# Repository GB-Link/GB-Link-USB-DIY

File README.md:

# GB-Link USB DIY: USB TO GAME BOY LINK ADAPTER

An Open-Source USB to Gameboy Link Cable Adapter for Raspberry Pi Pico. Designed with components that are easy to source and solder. Original design by agtbaskara. Link port footprint added by fairy0715. 
This board allows you to connect to GB/C or GBA games using a gereric GBC cable. OEM cables will work with their expected games.

# Required Components

| Reference | Part Number | Description |
|-|-|-|
| U1 | [Raspberry Pi Pico](https://www.raspberrypi.com/products/raspberry-pi-pico/) | Clones are compatible |
| U2 | [BOB-12009](https://www.sparkfun.com/products/12009) | Sparkfun Bi-Directional Logic Level Converter, clones are compatible |
| SW1 | [SS12D00-G3](https://www.amazon.com/Tnuocke-Vertical-Position-Switches-SS12D00-G3/dp/B099MRCDG8) | 3 Pin SPDT Switch with 1" (2.54mm) Pitch |

# Optional Case
Optional case available to print, works well in either PLA or PETG. No screws or glue needed.

https://www.printables.com/model/1805845-gb-link-v11-housing

# How to Order Board

To order a board, use the `gerbers.zip` from the release page or generate one yourself. You can order from your favourite PCB manufacturer ([JLCPCB](https://jlcpcb.com/), [PCBWay](https://www.pcbway.com/), etc.).

**Use 1.2mm PCB thickness.**

You can choose any colour for the Solder Mask and Silkscreen. For the Surface Finish, ENIG is highly recommended.

# How to Assemble Board

1. Sand the PCB edge connectors if necessary.
2. Solder pin header to Raspberry Pi Pico and Level Shifter module. Use a breadboard for easier pin soldering.
3. Solder Raspberry Pi Pico and Level Shifter module to the board
5. Solder the 1x3 Pin Header to the board, and place the Pin Jumper
6. Flash firmware to your Raspberry Pi Pico

Recomended firmware:
- [https://github.com/GB-Link/GBLink-Firmware/releases](https://github.com/GB-Link/GBLink-Firmware/releases)
List of clients for the GB-Link firmware found at [https://launcher.gblink.io/](https://launcher.gblink.io/)

Other compatible firmware:
- https://github.com/Celio-Link/Celio-Firmware
- https://github.com/Lorenzooone/pico-gb-mobile-adapter
- https://github.com/starlarkus/gb-link-firmware-reconfigurable
- https://github.com/stacksmashing/gb-link-firmware
- https://github.com/stacksmashing/gb-link-printer
- https://github.com/dj505/GBPrinterEmu
- https://github.com/Squaresweets/GBPrinter-discord-bot
- https://github.com/KuestenKeks/pc-to-gb-printer

- Raspberry Pi Pico Footprint: https://github.com/ncarandini/KiCad-RP-Pico
- Logic Level Converter (BOB-12009) Footprint: https://www.snapeda.com/parts/BOB-12009/SparkFun%20Electronics/view-part/
- Gameboy Link Connector Footprint: https://github.com/Palmr/gb-link-cable
- 1.2mm PCB Thickness, based on: https://hackaday.io/project/12932-game-link-online/log/43999-received-the-breakout-boards

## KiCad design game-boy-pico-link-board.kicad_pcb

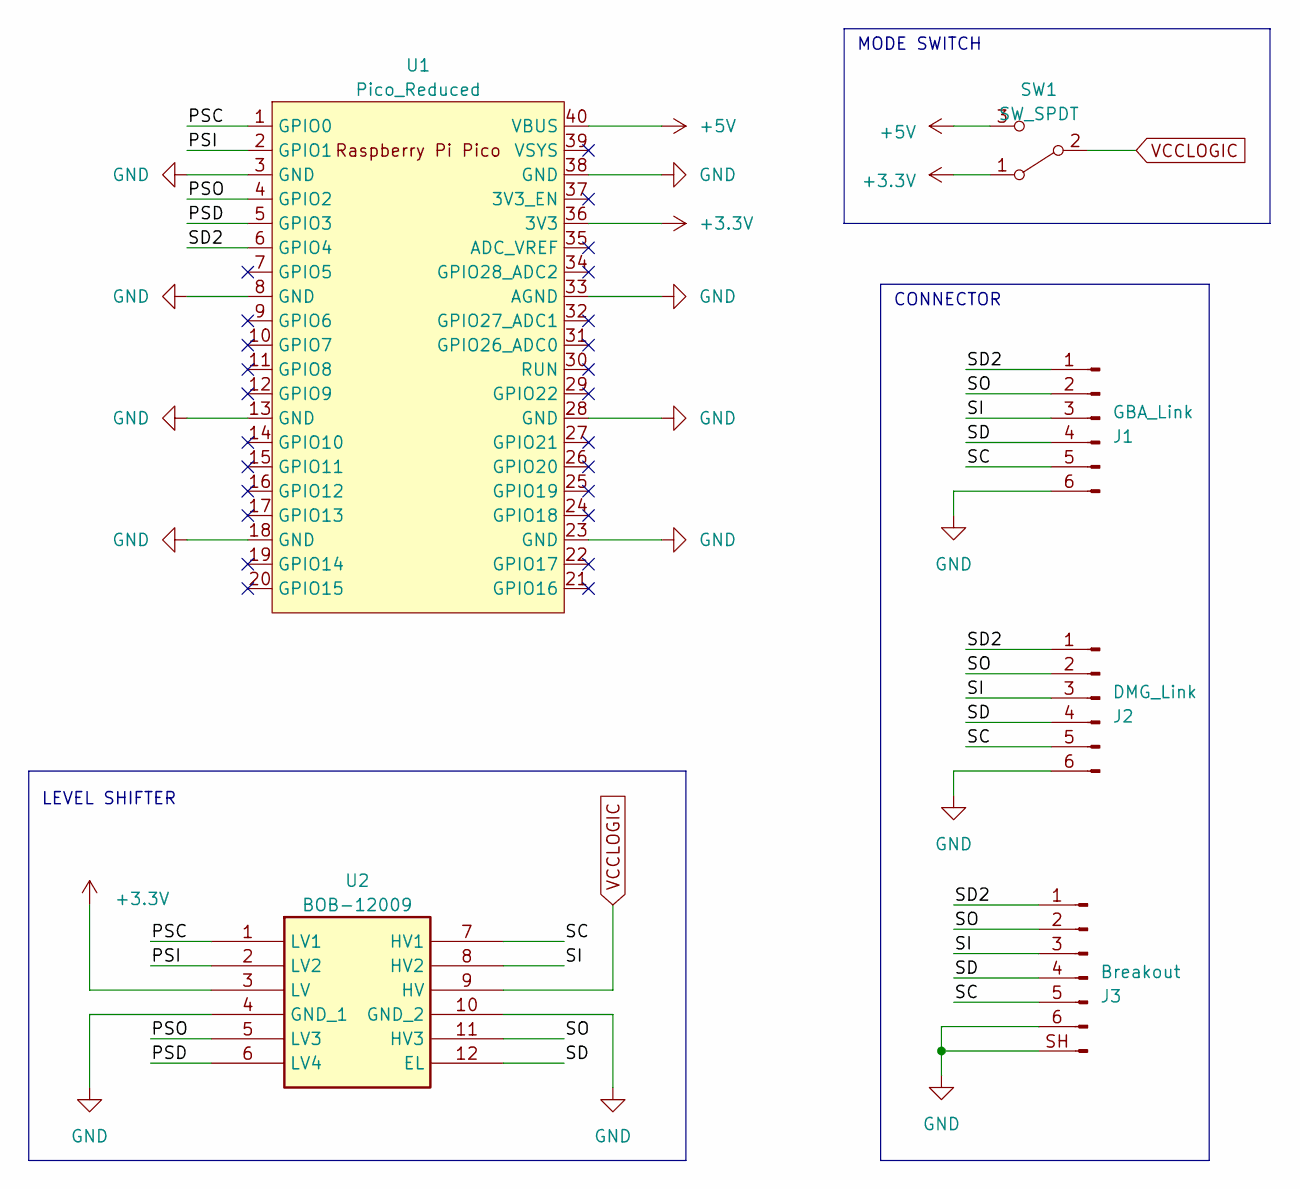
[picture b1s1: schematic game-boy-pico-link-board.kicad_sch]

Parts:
J1: GBA_Link; gb-link-socket
J2: DMG_Link; dmg-link-socket
J3: Breakout; gba_linkport
SW1: SW_SPDT; PinHeader_1x03_P2.54mm_Vertical
U1: Pico_Reduced; RPi_Pico_SMD_TH_REDUCED
U2: BOB-12009

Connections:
+3.3V: SW1.1 (A), U1.36 (3V3), U2.3 (LV)
+5V: SW1.3 (C), U1.40 (VBUS)
/GBVCC: J1.1, J2.1, J3.1, U1.6 (GPIO4)
/PSC: U1.1 (GPIO0), U2.1 (LV1)
/PSD: U1.5 (GPIO3), U2.6 (LV4)
/PSI: U1.2 (GPIO1), U2.2 (LV2)
/PSO: U1.4 (GPIO2), U2.5 (LV3)
/SC: J1.5, J2.5, J3.5, U2.7 (HV1)
/SD: J1.4, J2.4, J3.4, U2.12 (EL)
/SI: J1.3, J2.3, J3.3, U2.8 (HV2)
/SO: J1.2, J2.2, J3.2, U2.11 (HV3)
GND: J1.6, J2.6, J3.6, J3.SH (Pin_7), U1.3 (GND), U1.8 (GND), U1.13 (GND), U1.18 (GND), U1.23 (GND), U1.28 (GND), U1.33 (AGND), U1.38 (GND), U2.4 (GND_1), U2.10 (GND_2)
VCCLOGIC: SW1.2 (B), U2.9 (HV)

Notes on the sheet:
LEVEL SHIFTER
MODE SWITCH
CONNECTOR

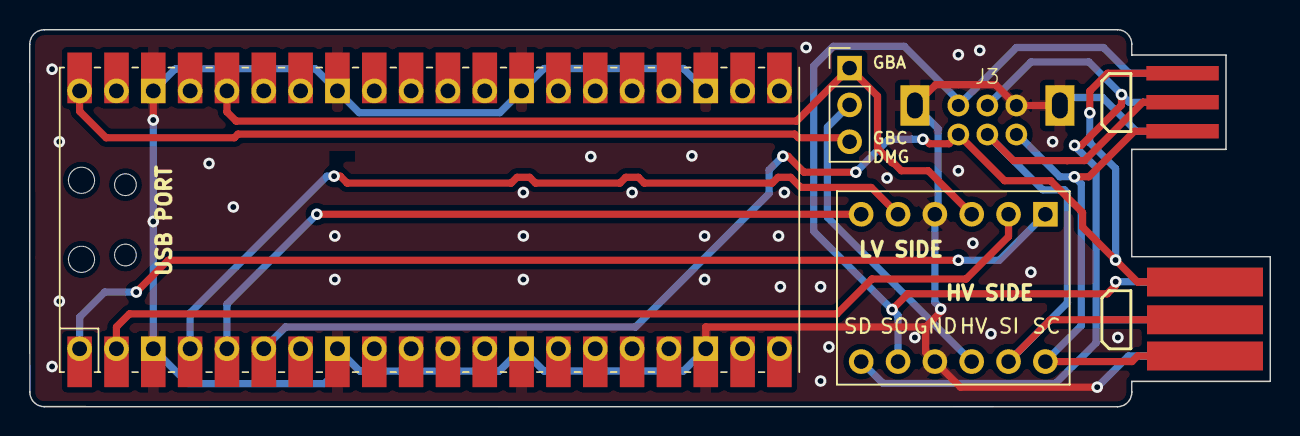
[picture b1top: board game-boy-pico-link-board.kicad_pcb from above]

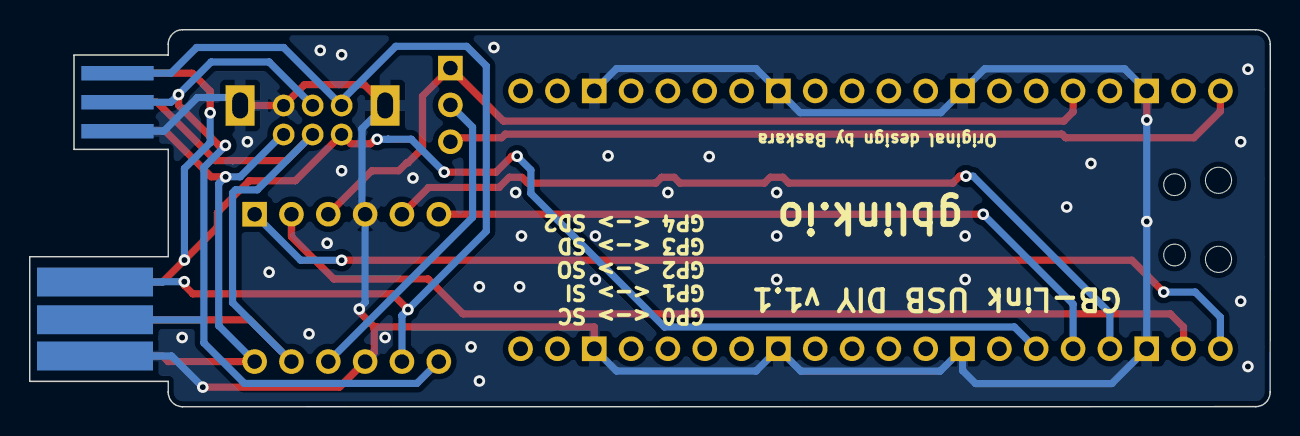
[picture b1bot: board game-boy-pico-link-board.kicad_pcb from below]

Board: 2 copper layers, 85.5 x 26.0 mm, 6 parts (2 on the bottom side), 13 nets.

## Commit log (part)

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2026-06-11 readmeを修正
